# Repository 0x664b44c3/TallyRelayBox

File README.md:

# TallyRelayBox
RS-422 Tally relay box using the TSL protocol

## Tally?

In broadcast the "red on air lamps" on cameras, monitors etc are called "Tally". They are one of the most basic and important means of communications in a studio.
Telling both the talent(s) and the technical crew (camera operators, director, etc) which image is on air (or about to be on air next).
This hardware design is a small project that fits into this niche by extracting eight channels of tally information from an RS-422/485 link carrying TSL UMD data. 
TSL's UMD protocol is one of the de-acto standards in "the industry" when it comes to distributing UMD - under monitor display - information (see tslproducts.com) 
with several other manufacturer's rack mount monitors or multy viewers understanding it.

This UMD data can easily be generated by a PC from your video mixer software (say OBS) or by writing an adapter application to translate your hardware mixer's protocol 
to TSL if the data link is not already using this protocol anyways.

The protocol obviously could be changed to whatever you feel is appropiate. Pull requests are welcome.

## Hardware

This design is based on a ATMega324PB.

Power supply can be in the range of 8 to 24V (change relays to your operating voltage!)

## Component sourcing

Most components in this design are widely available standard parts (Mouser etc are your friends for the switchmode regulator and inductor).
If used at 12V a 7805 linear regulator can be fitted as an alternative.
The provided CAD data allows easy adaption to your
local or preferred supplier. The board can be edited in the eagle freeware version if it is shortened by a few millimeters.
Current board size is designed to fit into a cheap plastic enclosure available from Reichelt Electronik in Germany 
(https://www.reichelt.de/kleingehaeuse-135-x-95-x-45-mm-eurobox-sw-p50429.html?&nbc=1). Similar enclosures should be readily available
from several suppliers. The relays used can either be TE  OJE-SS-112LMH or other types with a compatible footprint (like SonChuan 307 series).

## Compiling and flashing

I use avr-gcc 10.2.0 with GNU make on Linux for compiling this project. Your build environment may vary.
You may have to source the device definitions for the Mega324PB from Microchip to be able to compile this project.

See setup_fuses.sh for the fuse setting of the controller.

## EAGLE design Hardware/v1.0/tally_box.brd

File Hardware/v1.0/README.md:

Layout and schematics in EAGLE 6.0 file format.
This version still has an error in the RS-422 pinout (3/8 swapped)
A corrected version will be added later on.

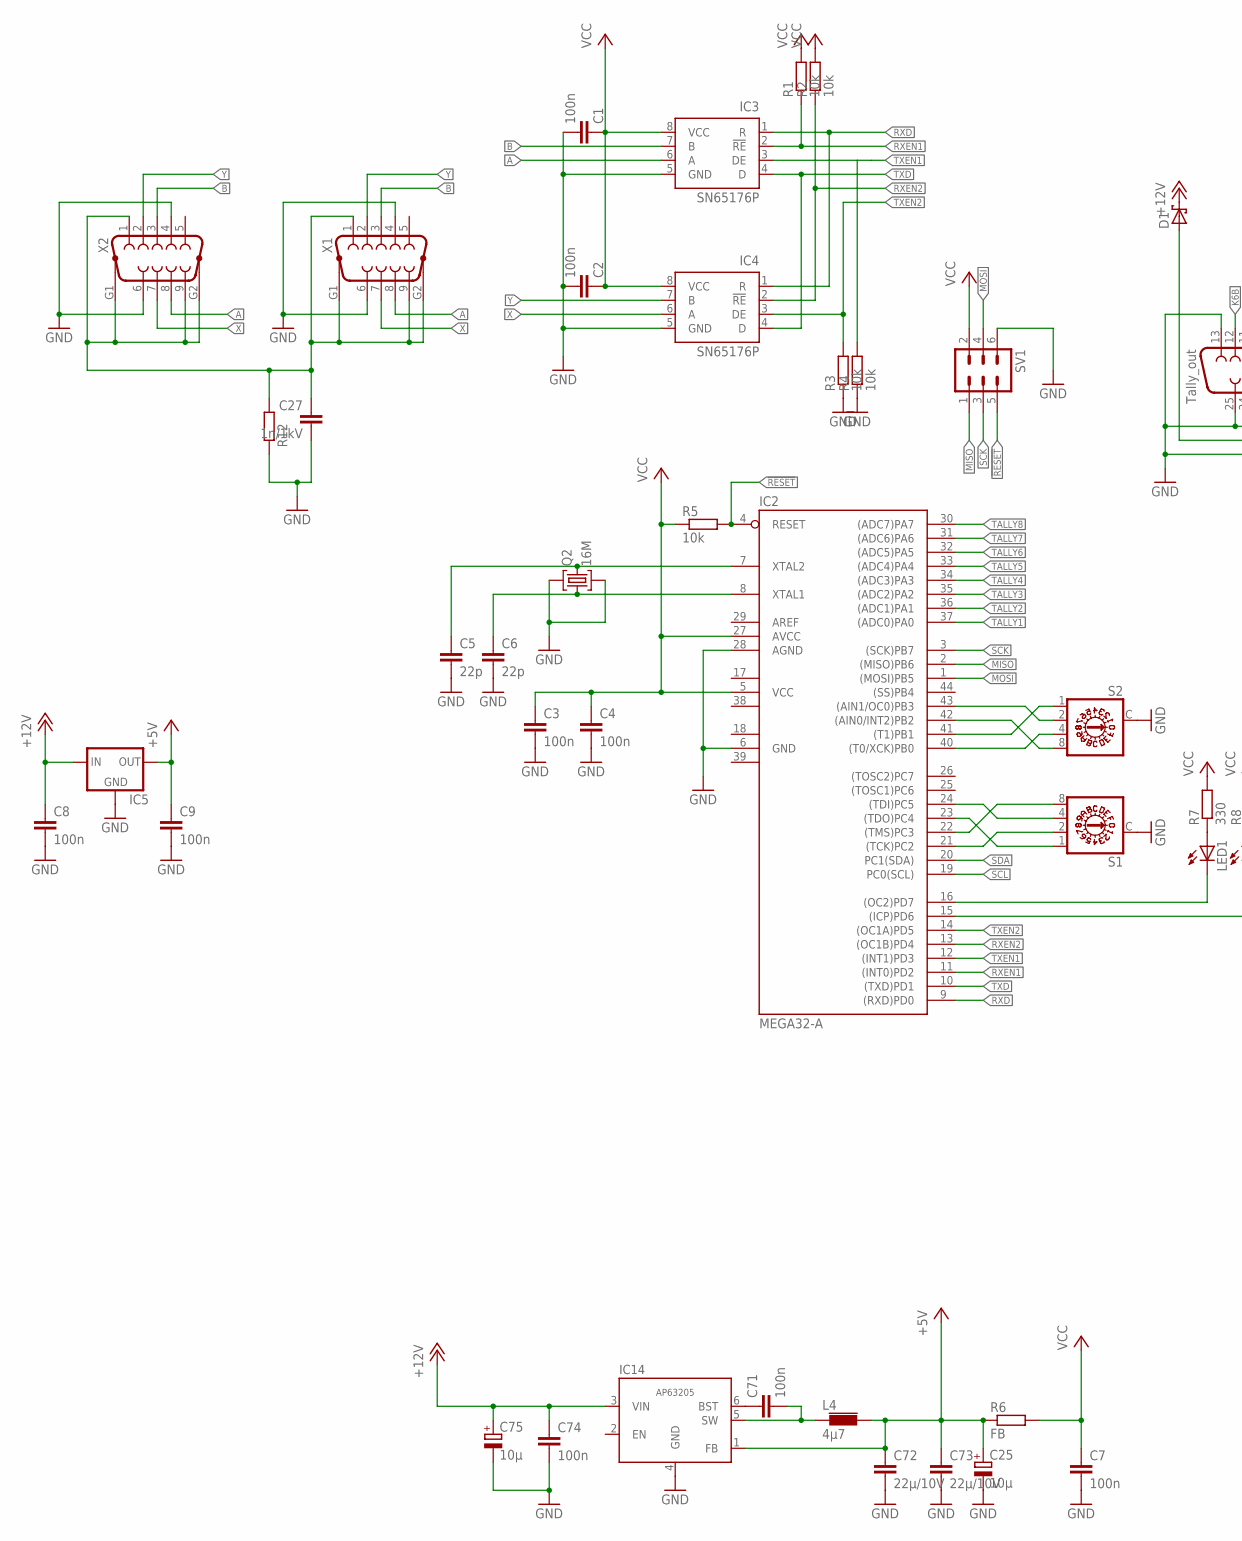
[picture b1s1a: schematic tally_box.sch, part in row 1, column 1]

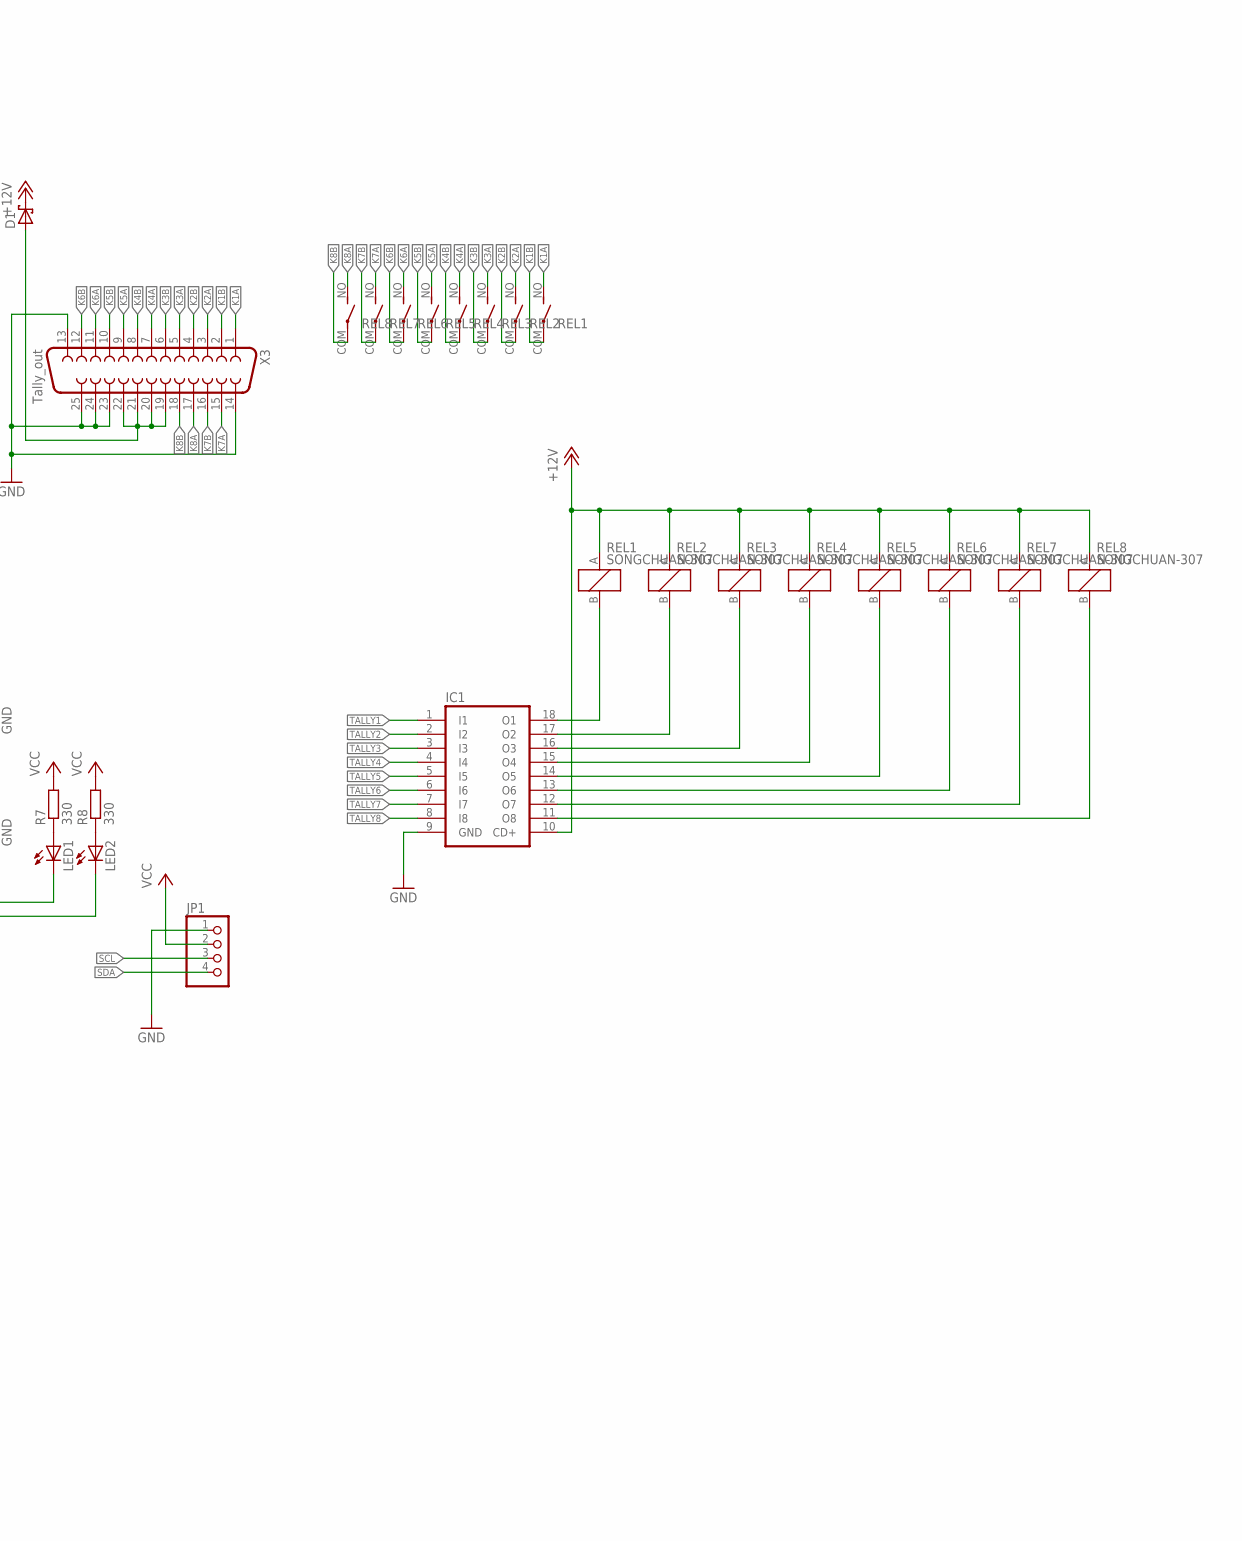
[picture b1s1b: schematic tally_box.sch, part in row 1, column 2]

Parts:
C1, C2, C3, C4, C7: 100n; C0603
C5, C6: 22p; C0603
C8, C9, C71, C74: 100n; C0805
C25: 10µ; PANASONIC_C
C27: 1n/1kV; C1206
C72, C73: 22µ/10V; C0805
C75: 10µ; PANASONIC_D
D1: SCHOTTKY-DIODESMD; SMB
IC1: ULN2803A; DIL18
IC2: MEGA32-A; TQFP44
IC3, IC4: SN65176P; DIL08
IC5: 78XXS
IC14: AP63205; SOT23-6L
JP1: PINHD-1X4; 1X04
L4: 4µ7; TYA4020
LED1, LED2: LED-TOPLED; P-LCC-2
Q2: 16M; MJ
R1, R2, R3, R4, R5: 10k; R0603
R6: FB; R0805
R7, R8: 330; R0603
R12: R-EU_R0603; R0603
REL1, REL2, REL3, REL4, REL5, REL6, REL7, REL8: SONGCHUAN-307; SONCHUAN-307
S1, S2: A1353HEX
SV1: ML6
X1, X2: F09HP
X3: Tally_out; F25HP

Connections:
!RESET!: IC2.4 (RESET), R5.2, SV1.5
+5V: C9.1, C25.+, C72.1, C73.1, IC5.OUT, IC14.1 (FB), L4.2, R6.1
+12V: C8.1, C74.1, C75.+, D1.C, IC1.10 (CD+), IC5.IN, IC14.3 (VIN), REL1.A (+), REL2.A (+), REL3.A (+), REL4.A (+), REL5.A (+), REL6.A (+), REL7.A (+), REL8.A (+)
A: IC3.6 (A), X1.8, X2.8
AREF: IC2.29 (AREF)
B: IC3.7 (B), X1.3, X2.3
GND: C1.2, C2.2, C3.2, C4.2, C5.2, C6.2, C7.2, C8.2, C9.2, C25.-, C27.2, C72.2, C73.2, C74.2, C75.-, IC1.9 (GND), IC2.6 (GND), IC2.28 (AGND), IC3.5 (GND), IC4.5 (GND), IC5.GND, IC14.4 (GND), JP1.1, Q2.2 (G1), Q2.4 (G2), R3.1, R4.1, R12.1, S1.C, S2.C, SV1.6, X1.4, X1.6, X2.4, X2.6, X3.13, X3.14, X3.23, X3.24, X3.25
GND1: IC2.18 (GND1)
GND2: IC2.39 (GND2)
K1A: REL1.NO (S), X3.1
K1B: REL1.COM, X3.2
K2A: REL2.NO (S), X3.3
K2B: REL2.COM, X3.4
K3A: REL3.NO (S), X3.5
K3B: REL3.COM, X3.6
K4A: REL4.NO (S), X3.7
K4B: REL4.COM, X3.8
K5A: REL5.NO (S), X3.9
K5B: REL5.COM, X3.10
K6A: REL6.NO (S), X3.11
K6B: REL6.COM, X3.12
K7A: REL7.NO (S), X3.15
K7B: REL7.COM, X3.16
K8A: REL8.NO (S), X3.17
K8B: REL8.COM, X3.18
MISO: IC2.2 ((MISO)PB6), SV1.1
MOSI: IC2.1 ((MOSI)PB5), SV1.4
unnamed: IC1.18 (O1), REL1.B (-)
unnamed: IC1.17 (O2), REL2.B (-)
unnamed: IC1.16 (O3), REL3.B (-)
unnamed: IC1.15 (O4), REL4.B (-)
unnamed: IC2.23 ((TDO)PC4), S1.1
unnamed: IC2.21 ((TCK)PC2), S1.2
unnamed: IC2.22 ((TMS)PC3), S1.8
unnamed: IC2.24 ((TDI)PC5), S1.4
unnamed: IC1.14 (O5), REL5.B (-)
unnamed: IC1.13 (O6), REL6.B (-)
unnamed: IC1.12 (O7), REL7.B (-)
unnamed: IC1.11 (O8), REL8.B (-)
unnamed: IC2.43 ((AIN1/OC0)PB3), S2.2
unnamed: D1.A, X3.19, X3.20, X3.21, X3.22
unnamed: IC2.42 ((AIN0/INT2)PB2), S2.8
unnamed: IC2.41 ((T1)PB1), S2.1
unnamed: IC2.40 ((T0/XCK)PB0), S2.4
unnamed: C5.1, IC2.7 (XTAL2), Q2.3 (2)
unnamed: C6.1, IC2.8 (XTAL1), Q2.1
unnamed: IC2.16 ((OC2)PD7), LED1.C
unnamed: IC2.15 ((ICP)PD6), LED2.C
unnamed: LED1.A, R7.1
unnamed: LED2.A, R8.1
unnamed: C71.1, IC14.6 (BST)
RXD: IC2.9 ((RXD)PD0), IC3.1 (R), IC4.1 (R)
RXEN1: IC2.11 ((INT0)PD2), IC3.2 (!RE), R1.1
RXEN2: IC2.13 ((OC1B)PD4), IC4.2 (!RE), R2.1
SCK: IC2.3 ((SCK)PB7), SV1.3
SCL: IC2.19 (PC0(SCL)), JP1.3
SDA: IC2.20 (PC1(SDA)), JP1.4
TALLY1: IC1.1 (I1), IC2.37 ((ADC0)PA0)
TALLY2: IC1.2 (I2), IC2.36 ((ADC1)PA1)
TALLY3: IC1.3 (I3), IC2.35 ((ADC2)PA2)
TALLY4: IC1.4 (I4), IC2.34 ((ADC3)PA3)
TALLY5: IC1.5 (I5), IC2.33 ((ADC4)PA4)
TALLY6: IC1.6 (I6), IC2.32 ((ADC5)PA5)
TALLY7: IC1.7 (I7), IC2.31 ((ADC6)PA6)
TALLY8: IC1.8 (I8), IC2.30 ((ADC7)PA7)
TXD: IC2.10 ((TXD)PD1), IC3.4 (D), IC4.4 (D)
TXEN1: IC2.12 ((INT1)PD3), IC3.3 (DE), R4.2
TXEN2: IC2.14 ((OC1A)PD5), IC4.3 (DE), R3.2
VCC: C1.1, C2.1, C3.1, C4.1, C7.1, IC2.5 (VCC), IC2.27 (AVCC), IC3.8 (VCC), IC4.8 (VCC), JP1.2, R1.2, R2.2, R5.1, R6.2, R7.2, R8.2, SV1.2
VCC1: IC2.17 (VCC1)
VCC2: IC2.38 (VCC2)
VSW_5V: C71.2, IC14.5 (SW), L4.1
X: IC4.6 (A), X1.7, X2.7
XGND: C27.1, R12.2, X1.1, X1.9, X1.G1, X1.G2, X2.1, X2.9, X2.G1, X2.G2
Y: IC4.7 (B), X1.2, X2.2

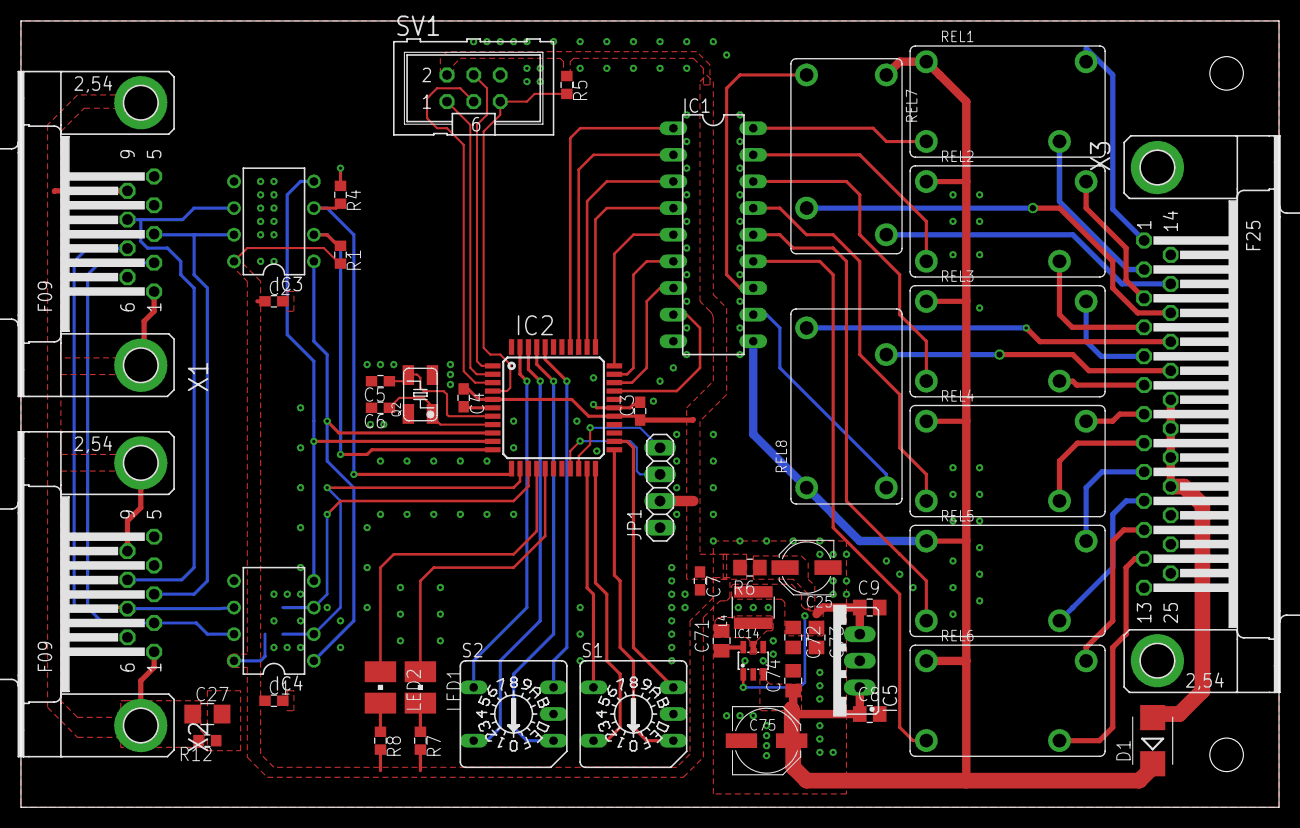
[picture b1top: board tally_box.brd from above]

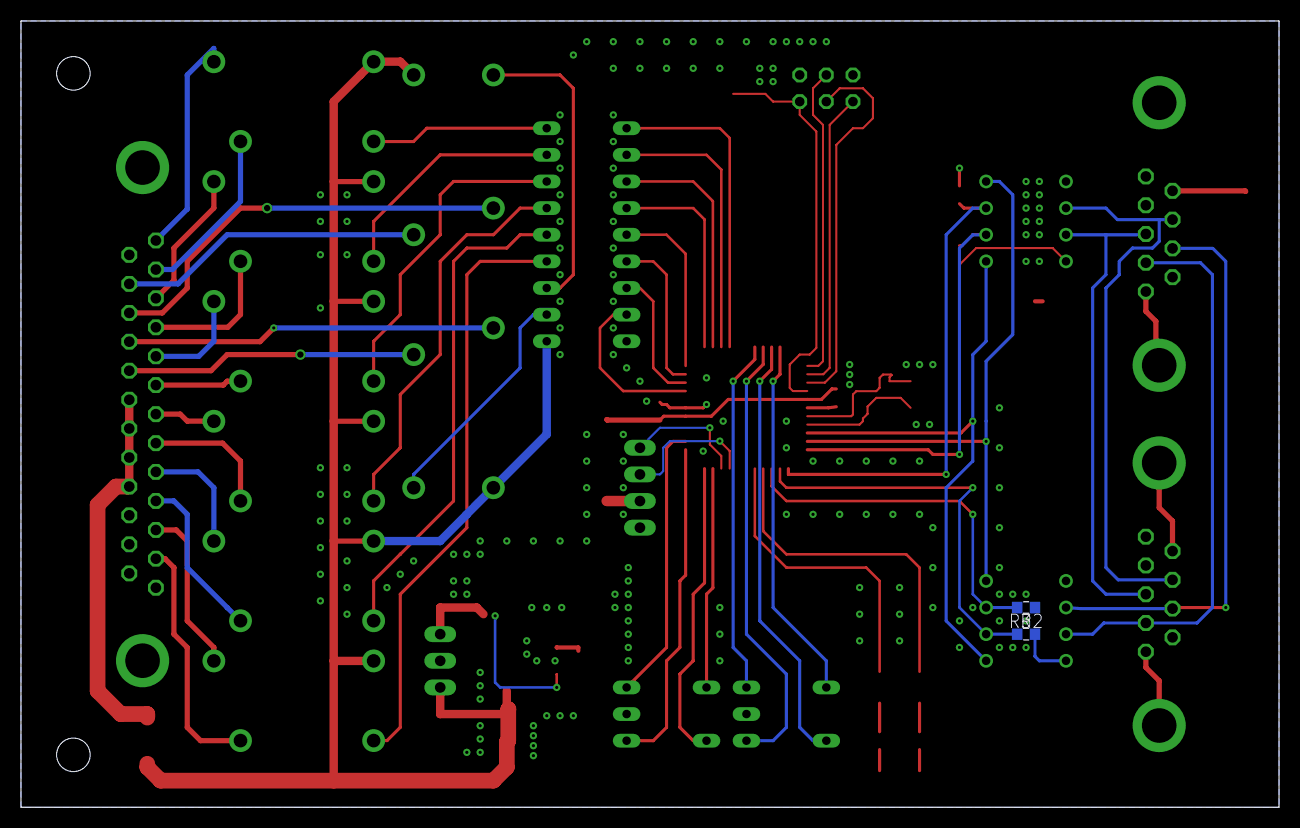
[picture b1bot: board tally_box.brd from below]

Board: 2 copper layers, 120.0 x 75.0 mm, 51 parts (2 on the bottom side), 70 nets.

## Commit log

2021-01-20 Added description
2021-01-20 Added Hardware
2021-01-20 Added descriptions on building and AVR fuse settings
2021-01-20 Added schematics PDF
2021-02-01 Some fixes
2021-02-19 added image of a (mostly) finished board
2021-02-19 Update README.md
    added image to description
